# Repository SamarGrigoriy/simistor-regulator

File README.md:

# Симисторный регулятор мощности (одноканальный)

Полный цикл разработки устройства под сетевую нагрузку: схема → печатная
плата в KiCad → параметрический корпус во FreeCAD → файлы для 3D-печати.
Регулятор рассчитан на длительную работу с током до 4 А.

> ⚠️ **Безопасность.** Устройство работает с сетевым напряжением 220 В.
> Повторяйте только при наличии опыта работы с силовой электроникой.
> Изоляция спроектирована по правилам усиленной изоляции, но готовое
> изделие требует проверки перед эксплуатацией.

---

## Возможности

- Управление активной нагрузкой до **4 А длительно** (симистор
  **BTA416Y-800C**, 3Q Hi-Com, с изолированным фланцем)
- Коммутация в момент перехода через ноль (**zero-cross**) — без
  импульсных помех в сеть
- Гальваническая развязка сетевой и низковольтной частей (оптроны
  **MOC3052**)
- ЖК-дисплей **1602 с I2C** и трёхкнопочное меню
- Датчик температуры по **1-Wire** с TVS-защитой на входе
- Питание МК от изолированного модуля **IRM-10-5** (5 В)
- Корпус для 3D-печати, генерируется скриптом под конкретную плату
- Разъём программатора (SWIO, +5V, GND, RX, TX) для прошивки и отладки

## Технические характеристики

| Параметр                | Основной вариант (3 А)           | Запасной (4 А)   |
| ----------------------- | -------------------------------- | ---------------- |
| Плата                   | 80 × 70 мм, 2 слоя, 1,6 мм       | то же            |
| Корпус                  | 87,9 × 75,8 × 46,1 мм            | 101 × 76 × 46 мм |
| Ток длительно\*         | 2,8 А (макс. потери по даташиту) | 4,1 А            |
| Радиатор                | ≈ 22 К/Вт                        | ≈ 14 К/Вт        |
| Изоляция сеть–НН        | ≥ 6,6 мм (усиленная)             | то же            |
| Функциональная изоляция | ≥ 2,5 мм                         | то же            |

\* При температуре воздуха в корпусе 40 °C и кристалле ≤ 110 °C, по
максимальным потерям BTA416Y-800C из даташита.

---

## Аппаратная часть

### Компоновка платы

- Все компоненты на верхней стороне; нижняя сторона чистая, плата
  лежит на стойках корпуса.
- **Сетевая часть** — левая колонка (симистор с радиатором, клеммники
  сети и нагрузки).
- **Низковольтная часть** — правая сторона (МК, дисплей, кнопки, датчик).
- Между ними — полоса развязки, через которую нет меди; оптроны
  установлены поперёк неё.
- Все клеммники на нижней кромке, провода вставляются через окна стенки
  корпуса.

### ЭМС и разводка

- Сплошная земля на нижнем слое в низковольтной части; верхний слой
  залит землёй; слои связаны 27 переходными.
- Питание МК — дерево без петель: `IRM → C201 → шина → МК / периферия`.
- Датчик: TVS-диод стоит первым от клеммника, его земля — переходным
  рядом.
- Конденсатор фильтра детектора нуля расположен у выхода оптрона.
- Силовые пути 4 А разведены дорожками 2 мм.

### Правила изоляции (проверены DRC)

| Правило                        | Минимум | Фактически |
| ------------------------------ | ------- | ---------- |
| Сеть — НН (усиленная изоляция) | 6,0 мм  | ≥ 6,6 мм   |
| Фаза / ноль / нагрузка (250 В) | 2,5 мм  | ≥ 2,5 мм   |
| Прочие сетевые цепи            | 1,0 мм  | ≥ 1,0 мм   |

**DRC: 0 ошибок, 0 неразведённых цепей.** Сверка со схемой — 0 расхождений.

---

## Корпус

Корпус строится **автоматически по файлу платы** скриптом `case.py`
(FreeCAD 1.1): считываются контур, отверстия, клеммники, симистор и
цепи сети/НН. Затем скрипт проверяет посадку и зазоры и выгружает
STL и STEP.

- Высота над платой 36 мм — рассчитывается по карте глубин всего, что
  висит на крышке (дисплей с переходником, провода, держатель, кнопки).
- Зазоры от сетевых деталей — не меньше **6 мм**, от остальных — 1 мм.
- Вентиляция: вход через щели левой стенки на уровне рёбер радиатора,
  выход — под дисплеем. Щели 1,6 мм (щуп ⌀2,5 не проходит).
- Крепление платы — 4 самореза в стойки дна; крышка — 4 самореза сбоку.
- Возможна подвеска на стену (два ключевых паза в низковольтной зоне).

### Детали для печати

| Файл                | Деталь            | Ориентация |
| ------------------- | ----------------- | ---------- |
| `base.stl`          | основание         | дном вниз  |
| `lid.stl`           | крышка            | лицом вниз |
| `button_holder.stl` | держатель кнопок  | плоскостью |
| `button_cap.stl`    | толкатель (3 шт.) | верхом     |

**Материал:** ABS/ASA или негорючий ABS/PC (V-0) — радиатор греется
до ~90 °C.

---

## Сборка из исходников

Плата **не правится напрямую** — она собирается из частей:

```bash
cd hw_1ch_v2

# Сборка файла платы из частей
head -n -2 build/placed.kicad_pcb > regulator1.kicad_pcb
cat routes/*.sexp >> regulator1.kicad_pcb
printf '\t(embedded_fonts no)\n)\n' >> regulator1.kicad_pcb

# Проверка правил проектирования
kicad-cli pcb drc --refill-zones --save-board \
    --severity-error -o build/drc_err.rpt regulator1.kicad_pcb
```

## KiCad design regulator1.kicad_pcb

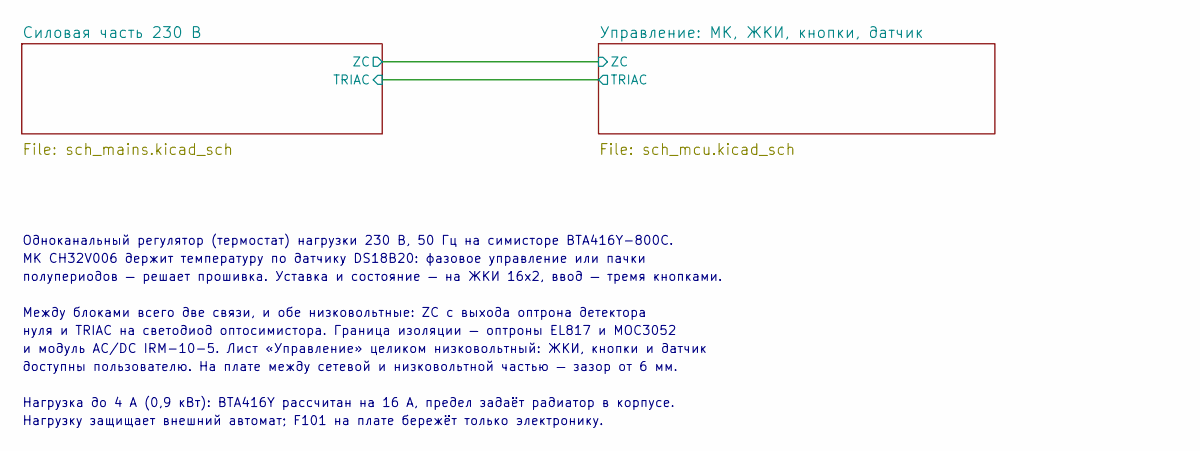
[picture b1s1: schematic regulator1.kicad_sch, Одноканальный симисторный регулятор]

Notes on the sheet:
Одноканальный регулятор (термостат) нагрузки 230 В, 50 Гц на симисторе BTA416Y-800C.
МК CH32V006 держит температуру по датчику DS18B20: фазовое управление или пачки
полупериодов — решает прошивка. Уставка и состояние — на ЖКИ 16x2, ввод — тремя кнопками.
Между блоками всего две связи, и обе низковольтные: ZC с выхода оптрона детектора
нуля и TRIAC на светодиод оптосимистора. Граница изоляции — оптроны EL817 и MOC3052
и модуль AC/DC IRM-10-5. Лист «Управление» целиком низковольтный: ЖКИ, кнопки и датчик
доступны пользователю. На плате между сетевой и низковольтной частью — зазор от 6 мм.
Нагрузка до 4 А (0,9 кВт): BTA416Y рассчитан на 16 А, предел задаёт радиатор в корпусе.
Нагрузку защищает внешний автомат; F101 на плате бережёт только электронику.

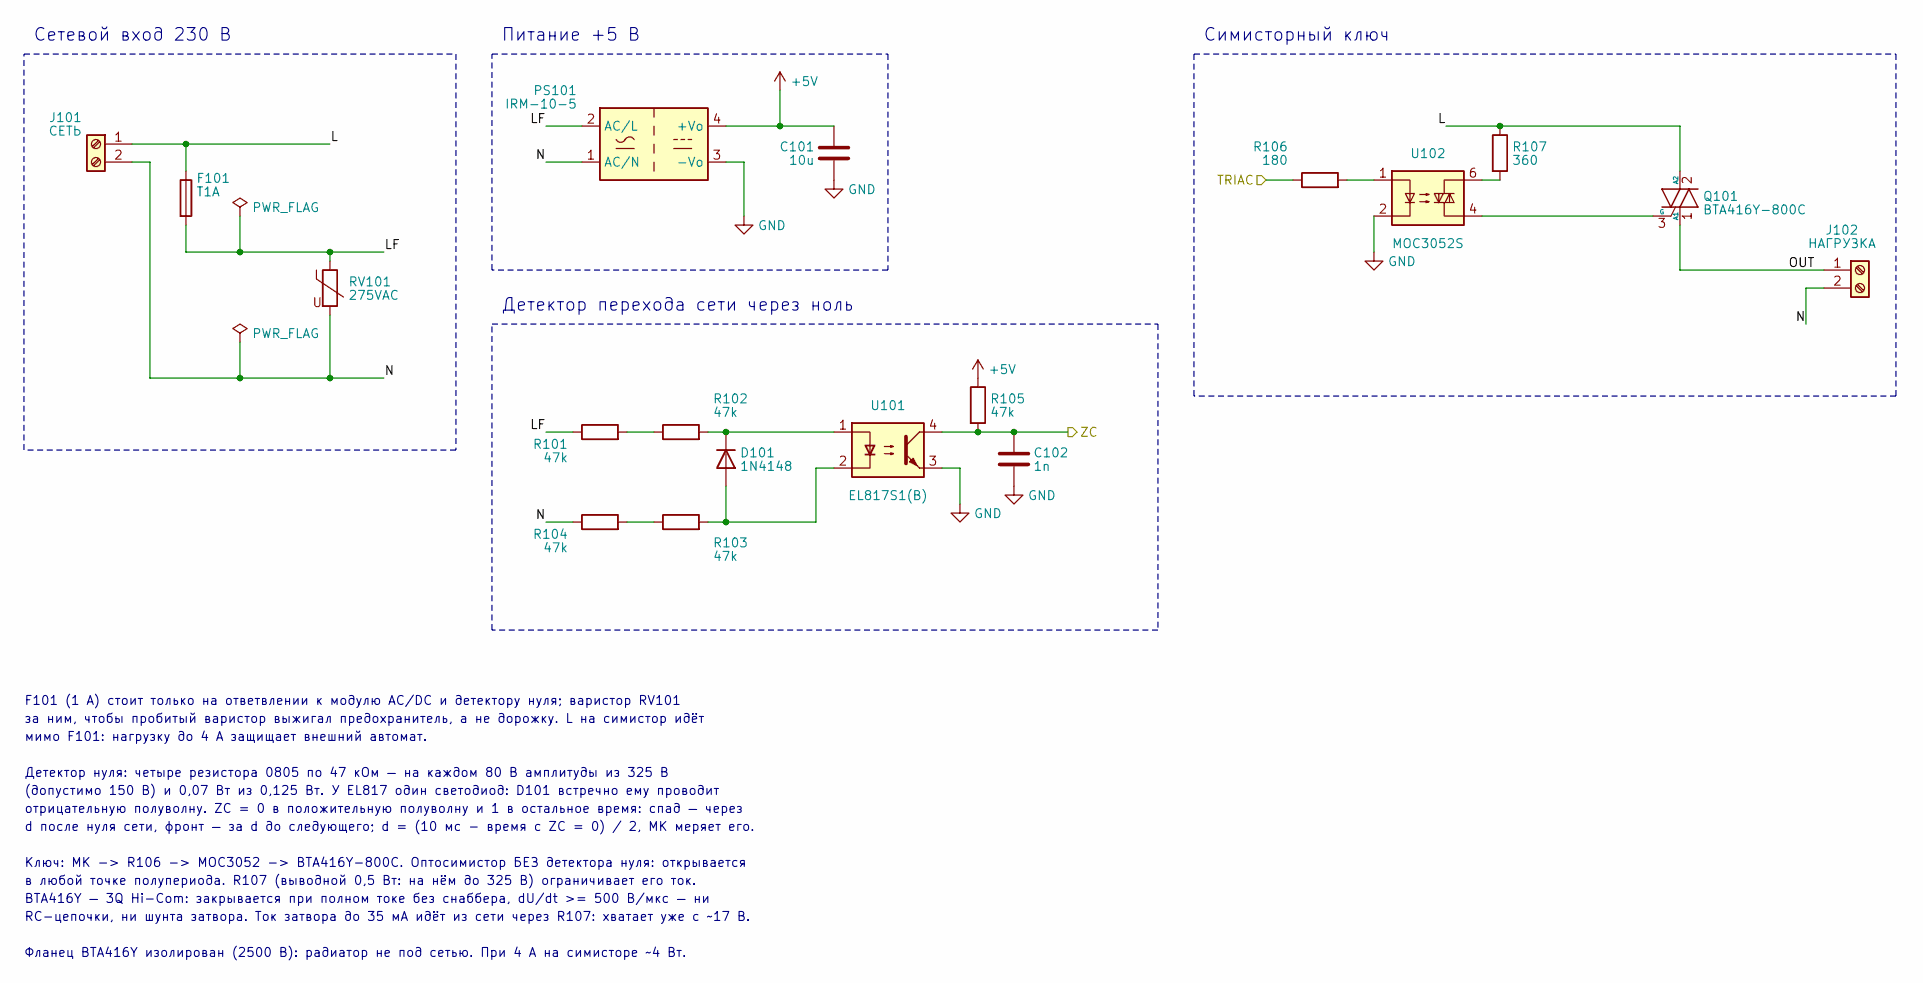
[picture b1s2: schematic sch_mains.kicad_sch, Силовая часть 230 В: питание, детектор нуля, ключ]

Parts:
C101: 10u; C_0805_2012Metric; MPN CL21A106KOQNNNE
C102: 1n; C_0805_2012Metric; MPN CC0805KRX7R9BB102
D101: 1N4148; D_DO-35_SOD27_P7.62mm_Horizontal; MPN 1N4148
F101: T1A; Fuse_Littelfuse_372_D8.50mm; MPN 37211000001
J101: СЕТЬ; TerminalBlock_Golten_GT301-5.0-02P_1x02_P5.00mm; MPN GT301-5.0-02P-12-00
J102: НАГРУЗКА; TerminalBlock_Golten_GT301-5.0-02P_1x02_P5.00mm; MPN GT301-5.0-02P-12-00
PS101: IRM-10-5; Converter_ACDC_MeanWell_IRM-10-xx_THT; MPN IRM-10-5
Q101: BTA416Y-800C; TO-220-3_Vertical; MPN BTA416Y-800C,127
R101, R102, R103, R104, R105: 47k; R_0805_2012Metric; MPN RC0805FR-0747KL
R106: 180; R_0805_2012Metric; MPN RC0805JR-07180RL
R107: 360; R_Axial_DIN0309_L9.0mm_D3.2mm_P12.70mm_Horizontal; MPN MFR-50JT-52-360R
RV101: 275VAC; RV_Disc_D12mm_W4.2mm_P7.5mm; MPN TSV10D431K
U101: EL817S1(B); SMDIP-4_W9.00mm_Everlight-EL817-S1; MPN EL817S1(B)(TU)-F
U102: MOC3052S; SMDIP-6_W9.00mm_LiteOn-MOC305xS; MPN MOC3052S-TA1

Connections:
+5V: C101.1, PS101.4 (+Vo), R105.1; also elsewhere on the board
/Силовая часть 230 В/L: F101.1, J101.1, Q101.2 (A2), R107.1
/Силовая часть 230 В/LF: F101.2, PS101.2 (AC/L), R101.1, RV101.1
/Силовая часть 230 В/N: J101.2, J102.2, PS101.1 (AC/N), R104.1, RV101.2
/Силовая часть 230 В/OUT: J102.1, Q101.1 (A1)
/Силовая часть 230 В/TRIAC: R106.1; also elsewhere on the board
/Силовая часть 230 В/ZC: C102.1, R105.2, U101.4; also elsewhere on the board
GND: C101.2, C102.2, PS101.3 (-Vo), U101.3, U102.2; also elsewhere on the board
unnamed: D101.2 (A), R103.2, U101.2
unnamed: D101.1 (K), R102.2, U101.1
unnamed: Q101.3 (G), U102.4
unnamed: R101.2, R102.1
unnamed: R103.1, R104.2
unnamed: R106.2, U102.1
unnamed: R107.2, U102.6

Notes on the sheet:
Сетевой вход 230 В
Питание +5 В
Детектор перехода сети через ноль
Симисторный ключ
F101 (1 А) стоит только на ответвлении к модулю AC/DC и детектору нуля; варистор RV101
за ним, чтобы пробитый варистор выжигал предохранитель, а не дорожку. L на симистор идёт
мимо F101: нагрузку до 4 А защищает внешний автомат.
Детектор нуля: четыре резистора 0805 по 47 кОм — на каждом 80 В амплитуды из 325 В
(допустимо 150 В) и 0,07 Вт из 0,125 Вт. У EL817 один светодиод: D101 встречно ему проводит
отрицательную полуволну. ZC = 0 в положительную полуволну и 1 в остальное время: спад — через
d после нуля сети, фронт — за d до следующего; d = (10 мс - время с ZC = 0) / 2, МК меряет его.
Ключ: МК -> R106 -> MOC3052 -> BTA416Y-800C. Оптосимистор БЕЗ детектора нуля: открывается
в любой точке полупериода. R107 (выводной 0,5 Вт: на нём до 325 В) ограничивает его ток.
BTA416Y — 3Q Hi-Com: закрывается при полном токе без снаббера, dU/dt >= 500 В/мкс — ни
RC-цепочки, ни шунта затвора. Ток затвора до 35 мА идёт из сети через R107: хватает уже с ~17 В.
Фланец BTA416Y изолирован (2500 В): радиатор не под сетью. При 4 А на симисторе ~4 Вт.

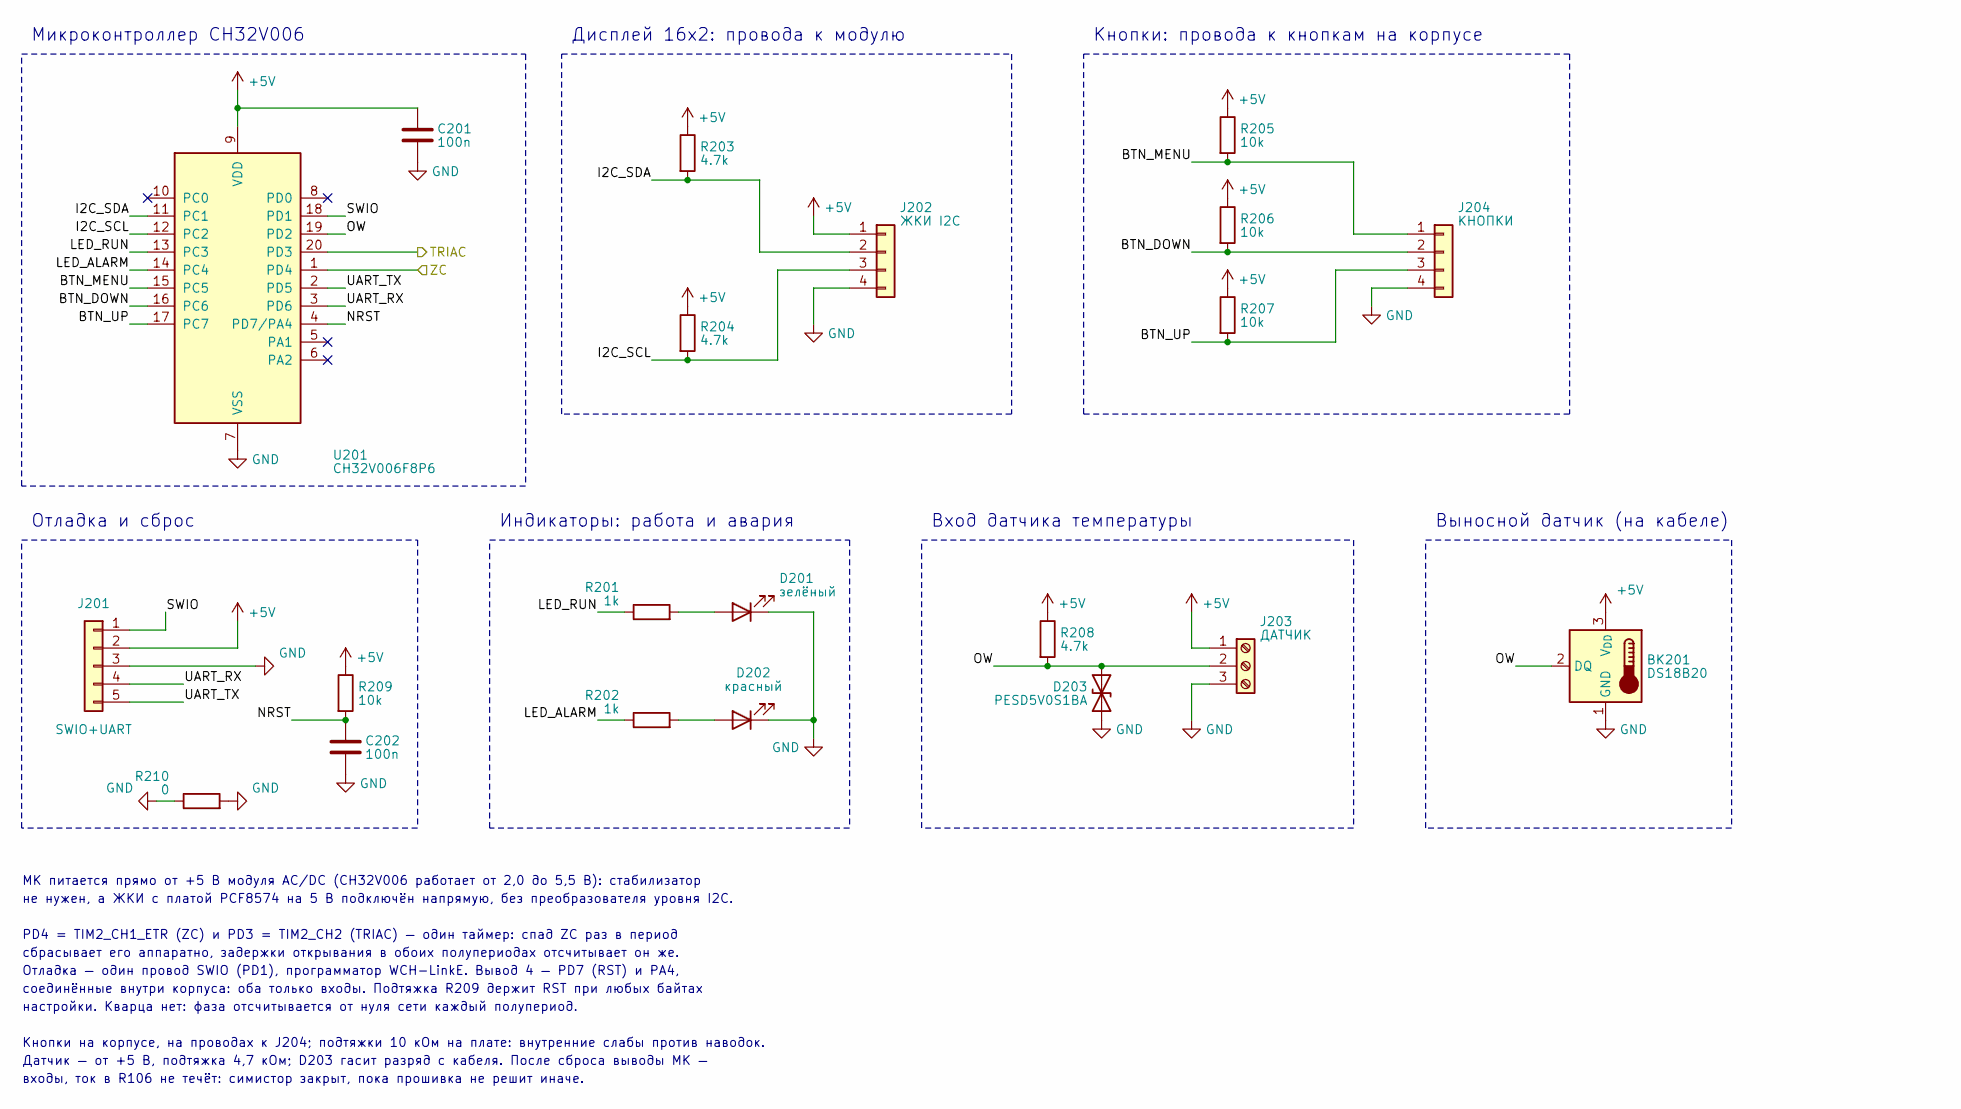
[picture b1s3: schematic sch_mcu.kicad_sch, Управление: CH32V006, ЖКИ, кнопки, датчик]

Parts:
BK201: DS18B20; MPN DS18B20 WATERPROOF TEMPERATURE SENSOR
C201, C202: 100n; C_0805_2012Metric; MPN CL21B104KBCNNNC
D201: зелёный; LED_0805_2012Metric; MPN LTST-C170KGKT
D202: красный; LED_0805_2012Metric; MPN LTST-C170KRKT
D203: PESD5V0S1BA; D_SOD-323; MPN PESD5V0S1BA,115
J201: SWIO+UART; PinHeader_1x05_P2.54mm_Vertical; MPN DS1021-1X5SF11-B
J202: ЖКИ I2C; SolderWire-0.25sqmm_1x04_P4.2mm_D0.65mm_OD1.7mm
J203: ДАТЧИК; TerminalBlock_Golten_GT301-5.0-03P_1x03_P5.00mm; MPN GT301-5.0-03P-12-00
J204: КНОПКИ; SolderWire-0.25sqmm_1x04_P4.2mm_D0.65mm_OD1.7mm
R201, R202: 1k; R_0805_2012Metric; MPN RC0805FR-071KL
R203, R204, R208: 4.7k; R_0805_2012Metric; MPN RC0805FR-074K7L
R205, R206, R207, R209: 10k; R_0805_2012Metric; MPN RC0805FR-0710KL
R210: 0; R_0805_2012Metric; MPN RC0805FR-070RL
U201: CH32V006F8P6; TSSOP-20_4.4x6.5mm_P0.65mm; MPN CH32V006F8P6; LCSC C52753342

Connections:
+5V: BK201.3 (V_{DD}), C201.1, J201.2, J202.1, J203.1, R203.1, R204.1, R205.1, R206.1, R207.1, R208.1, R209.1, U201.9 (VDD); also elsewhere on the board
/Силовая часть 230 В/TRIAC: U201.20 (PD3); also elsewhere on the board
/Силовая часть 230 В/ZC: U201.1 (PD4); also elsewhere on the board
/Управление: МК, ЖКИ, кнопки, датчик/BTN_DOWN: J204.2, R206.2, U201.16 (PC6)
/Управление: МК, ЖКИ, кнопки, датчик/BTN_MENU: J204.1, R205.2, U201.15 (PC5)
/Управление: МК, ЖКИ, кнопки, датчик/BTN_UP: J204.3, R207.2, U201.17 (PC7)
/Управление: МК, ЖКИ, кнопки, датчик/I2C_SCL: J202.3, R204.2, U201.12 (PC2)
/Управление: МК, ЖКИ, кнопки, датчик/I2C_SDA: J202.2, R203.2, U201.11 (PC1)
/Управление: МК, ЖКИ, кнопки, датчик/LED_ALARM: R202.1, U201.14 (PC4)
/Управление: МК, ЖКИ, кнопки, датчик/LED_RUN: R201.1, U201.13 (PC3)
/Управление: МК, ЖКИ, кнопки, датчик/NRST: C202.1, R209.2, U201.4 (PD7/PA4)
/Управление: МК, ЖКИ, кнопки, датчик/OW: BK201.2 (DQ), D203.2 (A2), J203.2, R208.2, U201.19 (PD2)
/Управление: МК, ЖКИ, кнопки, датчик/SWIO: J201.1, U201.18 (PD1)
/Управление: МК, ЖКИ, кнопки, датчик/UART_RX: J201.4, U201.3 (PD6)
/Управление: МК, ЖКИ, кнопки, датчик/UART_TX: J201.5, U201.2 (PD5)
GND: BK201.1 (GND), C201.2, C202.2, D201.1 (K), D202.1 (K), D203.1 (A1), J201.3, J202.4, J203.3, J204.4, R210.1, R210.2, U201.7 (VSS); also elsewhere on the board
unnamed: D201.2 (A), R201.2
unnamed: D202.2 (A), R202.2

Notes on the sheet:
Микроконтроллер CH32V006
Дисплей 16x2: провода к модулю
Кнопки: провода к кнопкам на корпусе
Отладка и сброс
Индикаторы: работа и авария
Вход датчика температуры
Выносной датчик (на кабеле)
МК питается прямо от +5 В модуля AC/DC (CH32V006 работает от 2,0 до 5,5 В): стабилизатор
не нужен, а ЖКИ с платой PCF8574 на 5 В подключён напрямую, без преобразователя уровня I2C.
PD4 = TIM2_CH1_ETR (ZC) и PD3 = TIM2_CH2 (TRIAC) — один таймер: спад ZC раз в период
сбрасывает его аппаратно, задержки открывания в обоих полупериодах отсчитывает он же.
Отладка — один провод SWIO (PD1), программатор WCH-LinkE. Вывод 4 — PD7 (RST) и PA4,
соединённые внутри корпуса: оба только входы. Подтяжка R209 держит RST при любых байтах
настройки. Кварца нет: фаза отсчитывается от нуля сети каждый полупериод.
Кнопки на корпусе, на проводах к J204; подтяжки 10 кОм на плате: внутренние слабы против наводок.
Датчик — от +5 В, подтяжка 4,7 кОм; D203 гасит разряд с кабеля. После сброса выводы МК —
входы, ток в R106 не течёт: симистор закрыт, пока прошивка не решит иначе.

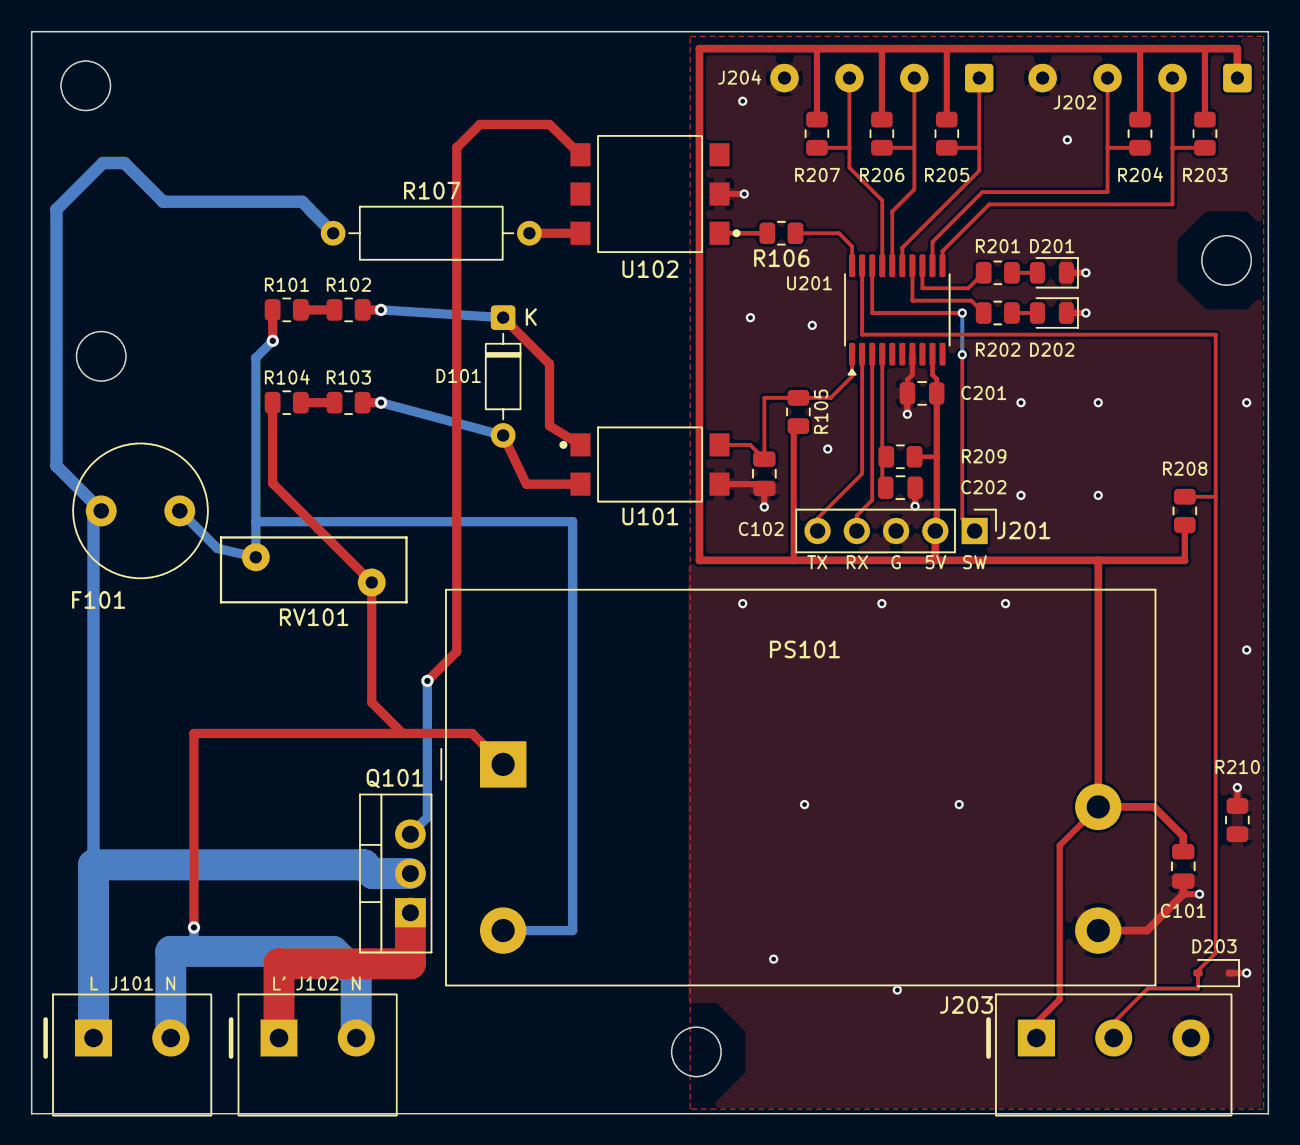
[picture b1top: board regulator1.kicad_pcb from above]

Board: 2 copper layers, 80.0 x 70.0 mm, 38 parts (0 on the bottom side), 29 nets.
